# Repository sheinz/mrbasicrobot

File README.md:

mrbasicrobot
============

A robot based on Dagu Mr Basic platform.

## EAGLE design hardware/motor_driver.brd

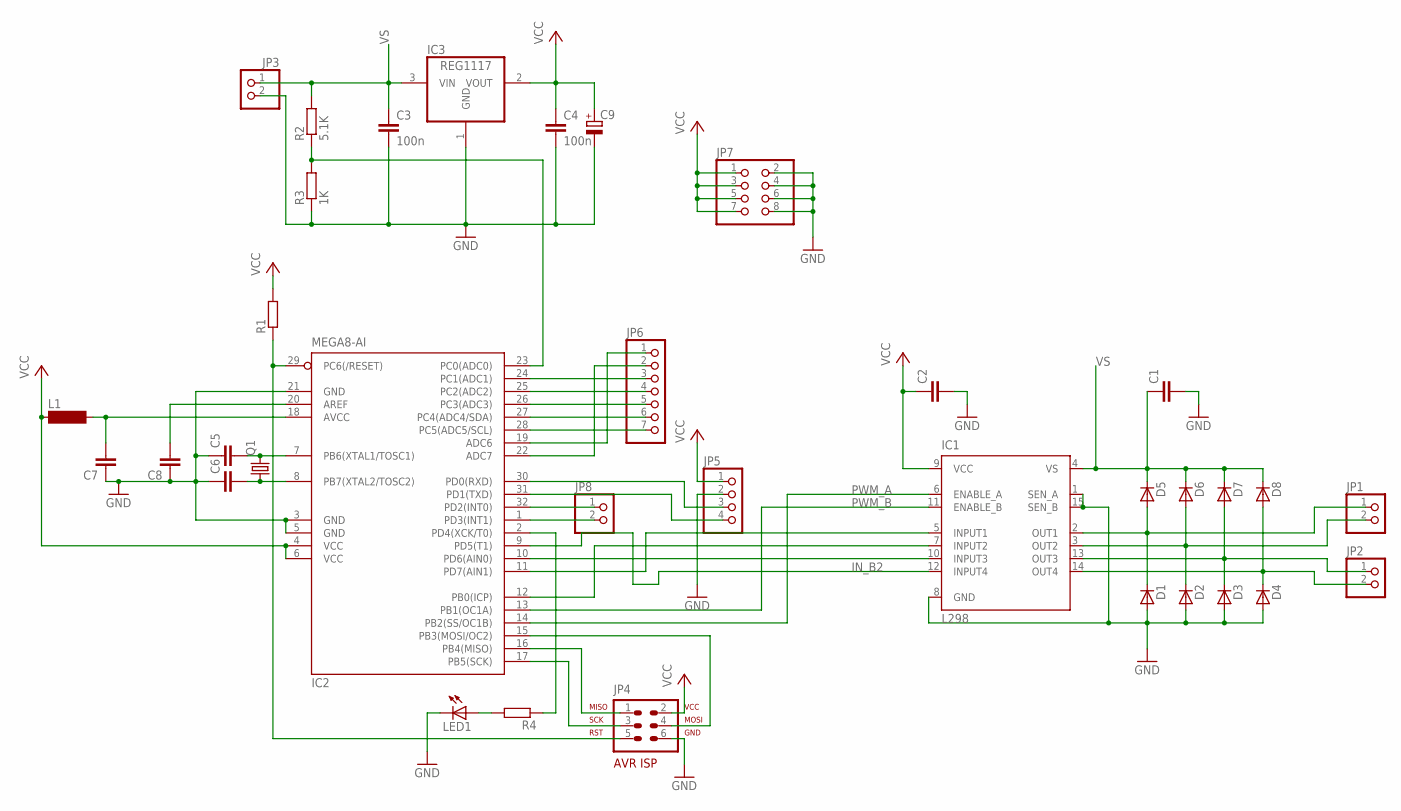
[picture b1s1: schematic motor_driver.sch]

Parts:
C1, C2, C5, C6, C7, C8: C-EUC0805; C0805
C3, C4: 100n; C0805
C9: CPOL-EUE2,5-6E; E2,5-6E
D1, D2, D3, D4, D5, D6, D7, D8: BYS10; SOD106A
IC1: L298; MULTIWATT-15
IC2: MEGA8-AI; TQFP32-08
IC3: REG1117; SOT223
JP1, JP2, JP3, JP8: PINHD-1X2; 1X02
JP4: AVR-ISP-6VERT; AVR-ISP-6
JP5: PINHD-1X4; 1X04
JP6: PINHD-1X7; 1X07
JP7: PINHD-2X4; 2X04
L1: SM-1206
LED1: LED3MM
Q1: CRYSTALHC49S; HC49/S
R1, R4: R-EU_M0805; M0805
R2: 5.1K; M0805
R3: 1K; M0805

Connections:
GND: C1.2, C2.2, C3.2, C4.2, C5.1, C6.1, C7.1, C8.1, C9.-, D1.A, D2.A, D3.A, D4.A, IC1.1 (SEN_A), IC1.8 (GND), IC1.15 (SEN_B), IC2.3 (GND), IC2.5 (GND), IC2.21 (GND), IC3.1 (GND), JP3.2, JP4.6, JP5.2, JP7.2, JP7.4, JP7.6, JP7.8, LED1.K (C), R3.1
IN_B2: IC1.12 (INPUT4), IC2.9 (PD5(T1))
unnamed: D1.K, D5.A, IC1.2 (OUT1), JP1.1
unnamed: D2.K, D6.A, IC1.3 (OUT2), JP1.2
unnamed: D3.K, D7.A, IC1.13 (OUT3), JP2.1
unnamed: D4.K, D8.A, IC1.14 (OUT4), JP2.2
unnamed: IC2.16 (PB4(MISO)), JP4.1
unnamed: IC2.17 (PB5(SCK)), JP4.3
unnamed: IC2.15 (PB3(MOSI/OC2)), JP4.4
unnamed: C5.2, IC2.7 (PB6(XTAL1/TOSC1)), Q1.2
unnamed: IC2.23 (PC0(ADC0)), R2.1, R3.2
unnamed: IC2.29 (PC6(/RESET)), JP4.5, R1.1
unnamed: C6.2, IC2.8 (PB7(XTAL2/TOSC2)), Q1.1
unnamed: IC2.30 (PD0(RXD)), JP5.3
unnamed: C7.2, IC2.18 (AVCC), L1.2
unnamed: C8.2, IC2.20 (AREF)
unnamed: IC2.31 (PD1(TXD)), JP5.4
unnamed: IC2.28 (PC5(ADC5/SCL)), JP6.7
unnamed: IC2.27 (PC4(ADC4/SDA)), JP6.6
unnamed: IC2.26 (PC3(ADC3)), JP6.5
unnamed: IC2.25 (PC2(ADC2)), JP6.4
unnamed: IC2.24 (PC1(ADC1)), JP6.3
unnamed: IC2.19 (ADC6), JP6.1
unnamed: IC2.22 (ADC7), JP6.2
unnamed: IC2.2 (PD4(XCK/T0)), R4.1
unnamed: IC1.7 (INPUT2), IC2.12 (PB0(ICP))
unnamed: IC1.5 (INPUT1), IC2.11 (PD7(AIN1))
unnamed: IC1.10 (INPUT3), IC2.10 (PD6(AIN0))
unnamed: LED1.A, R4.2
unnamed: IC2.32 (PD2(INT0)), JP8.1
unnamed: IC2.1 (PD3(INT1)), JP8.2
PWM_A: IC1.11 (ENABLE_B), IC2.13 (PB1(OC1A))
PWM_B: IC1.6 (ENABLE_A), IC2.14 (PB2(SS/OC1B))
VCC: C2.1, C4.1, C9.+, IC1.9 (VCC), IC2.4 (VCC), IC2.6 (VCC), IC3.2 (VOUT), JP4.2, JP5.1, JP7.1, JP7.3, JP7.5, JP7.7, L1.1, R1.2
VS: C1.1, C3.1, D5.K, D6.K, D7.K, D8.K, IC1.4 (VS), IC3.3 (VIN), JP3.1, R2.2

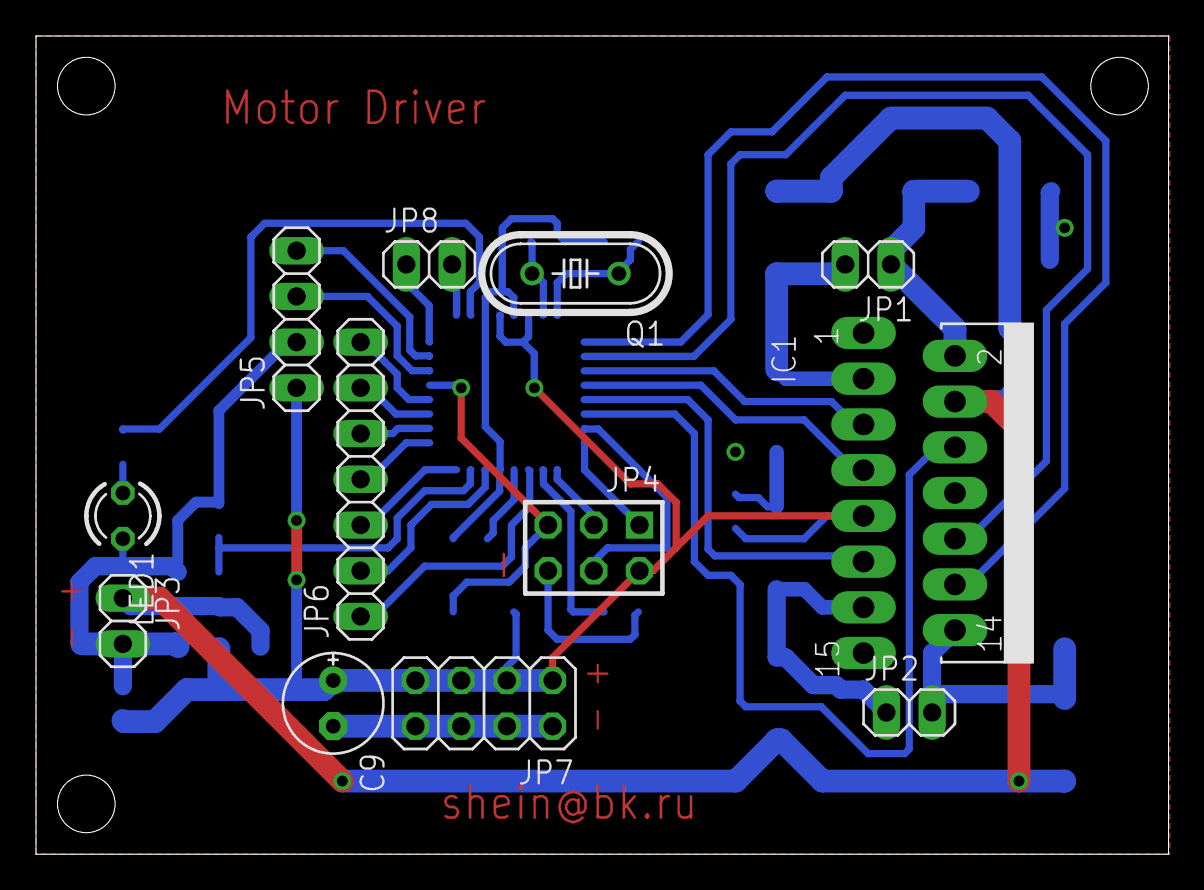
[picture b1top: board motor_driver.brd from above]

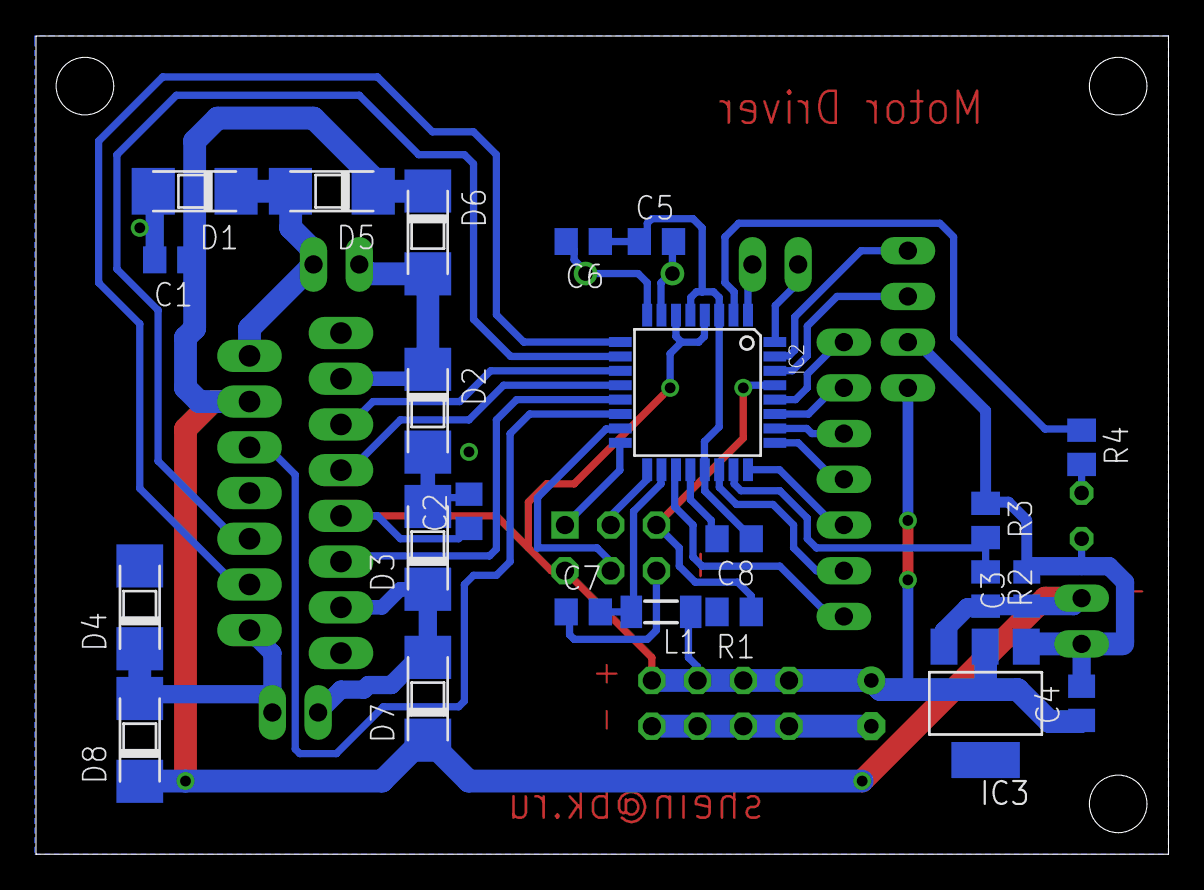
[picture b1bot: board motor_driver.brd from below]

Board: 2 copper layers, 62.9 x 45.5 mm, 35 parts (23 on the bottom side), 35 nets.

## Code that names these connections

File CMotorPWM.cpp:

/*
   The class uses Timer/Counter1 to orginise 2 channel PWM in order to control 2 motors

*/


#include "CMotorPWM.h"
#include <avr/io.h>
#include <avr/interrupt.h>


// hardware configuration
#define OUT_1_DDR      DDRD
#define OUT_1_PORT     PORTD
#define OUT_1_PIN      _BV(PD7)

#define OUT_2_DDR      DDRB
#define OUT_2_PORT     PORTB
#define OUT_2_PIN      _BV(PB0)

#define OUT_3_DDR      DDRD
#define OUT_3_PORT     PORTD
#define OUT_3_PIN      _BV(PD6)

#define OUT_4_DDR      DDRD
#define OUT_4_PORT     PORTD
#define OUT_4_PIN      _BV(PD5)

#define PWM_DDR        DDRB
#define PWM_PORT       PORTB
#define PWM_A_PIN      _BV(PB1)
#define PWM_B_PIN      _BV(PB2)

//    Motor PWM configuration
//    Motor A  - PB1
//    Motor B  - PB2


#define START_TIMER()      TCCR2 |= _BV(CS21) | _BV(CS22)   // Normal mode, prescaler F_CPU/8
#define STOP_TIMER()       TCCR2 = 0            // Stop timer

// clear the interrupt flag in case the interrupt has already occurred
#define ENABLE_OVERFLOW_INT()      TIFR |= _BV(TOV2); TIMSK |= _BV(TOIE2); TIMSK &= ~_BV(OCIE2)        // enable overflow
#define ENABLE_COMPARE_INT()       TIFR |= _BV(OCF2); TIMSK |= _BV(OCIE2); TIMSK &= ~_BV(TOIE2)    

CMotorPWM::eMotorMode CMotorPWM::mMotorMode[CMotorPWM::MOTOR_COUNT];
uint8_t CMotorPWM::mMotorSpeed[CMotorPWM::MOTOR_COUNT];
CMotorPWM::PwmChannel CMotorPWM::mPwm[CMotorPWM::MOTOR_COUNT];
int8_t CMotorPWM::mCurrentPwm;
CMotorPWM::PwmChannel CMotorPWM::mPwmUpd[CMotorPWM::MOTOR_COUNT];
volatile bool CMotorPWM::mUpdate;


// ----------------------------------------------------------------------------

ISR(TIMER2_COMP_vect)
{
   STOP_TIMER();
   TCNT2 = OCR2;     // reset the interrupt overhead

   PWM_PORT &= ~(CMotorPWM::mPwm[CMotorPWM::mCurrentPwm].mask);
  
   CMotorPWM::mCurrentPwm++;

   if (  (CMotorPWM::mCurrentPwm < CMotorPWM::MOTOR_COUNT) && 
         (CMotorPWM::mPwm[CMotorPWM::mCurrentPwm].mask != 0)   )
   {
      OCR2 = CMotorPWM::mPwm[CMotorPWM::mCurrentPwm].value;
   }
   else
   {
      //if (OCR2 == 0xFF) TCNT2 = 0xFF;     // so the next interrupt will be immediately 

      CMotorPWM::mCurrentPwm = 0;
      ENABLE_OVERFLOW_INT();
   }  


   START_TIMER();
}

// ----------------------------------------------------------------------------

ISR(TIMER2_OVF_vect)
{   
   uint8_t mask = 0;
   STOP_TIMER();
   TCNT2 = 0;        // reset interrupt overhead

   // update 
   if (CMotorPWM::mUpdate)
   {
      PORTC |= _BV(PC3);

      for (uint8_t i = 0; i < CMotorPWM::MOTOR_COUNT; i++)
      {
         CMotorPWM::mPwm[i].mask = CMotorPWM::mPwmUpd[i].mask;
         CMotorPWM::mPwm[i].value = CMotorPWM::mPwmUpd[i].value;
      }
      CMotorPWM::mUpdate = false;
   }
   
   if (CMotorPWM::mPwm[0].value == 0)
   {
      mask = CMotorPWM::mPwm[0].mask;
      CMotorPWM::mCurrentPwm = 1;   
   }
   
   OCR2 = CMotorPWM::mPwm[CMotorPWM::mCurrentPwm].value;    // it can be 0xFF

   PWM_PORT |= (PWM_A_PIN | PWM_B_PIN) & (~mask);  // set all pins except for the value=0
   
   ENABLE_COMPARE_INT();
   START_TIMER();
}

// ----------------------------------------------------------------------------

void CMotorPWM::init(void)
{
   // Set all control port to output
   OUT_1_DDR |= OUT_1_PIN;
   OUT_2_DDR |= OUT_2_PIN;
   OUT_3_DDR |= OUT_3_PIN;
   OUT_4_DDR |= OUT_4_PIN;

   PWM_DDR |= PWM_A_PIN | PWM_B_PIN; // the PWM pins must be set as output


   for (uint8_t i = 0; i < MOTOR_COUNT; i++)
   {
      mMotorSpeed[i] = 127;
      mMotorMode[i] = IDLE; 
   }
   
   mPwm[0].mask = PWM_A_PIN | PWM_B_PIN;
   mPwm[0].value = 127;
   mPwm[1].mask = 0;    // 0 means this is the terminal element
   mPwm[1].value = 0xFF;
   mPwmUpd[0] = mPwm[0];
   mPwmUpd[1] = mPwm[1];
   mUpdate = false;

   CMotorPWM::mCurrentPwm = 0;

   TCNT2 = 250;         // next interrupt will be the overflow
   OCR2 = 127;          // somewhere in the middle
   ENABLE_OVERFLOW_INT();
   START_TIMER();
}

// ----------------------------------------------------------------------------

void CMotorPWM::setMotor(const CMotorPWM::eMotor motor, const CMotorPWM::eMotorMode mode)
{
   if (motor < MOTOR_COUNT)
   {
      mMotorMode[motor] = mode;

      if (mode == IDLE)
      {
         mMotorSpeed[motor] = 0;
         updateMotorsSpeed();
      }
      else if (mode == FORWARD)
      {
         setDirection(motor, true, false);
         updateMotorsSpeed();
      }
      else if (mode == BACKWARD)
      {
         setDirection(motor, false, true);
         updateMotorsSpeed();
      }
      else if (mode == BRAKE)
      {
         setDirection(motor, false, false);
         mMotorSpeed[motor] = 0xFF;
         updateMotorsSpeed();
      }
   }   
}

// ----------------------------------------------------------------------------

void CMotorPWM::setMotor(const CMotorPWM::eMotor motor, const CMotorPWM::eMotorMode mode, const uint8_t speed)
{
   if (motor < MOTOR_COUNT)
   {
      mMotorSpeed[motor] = speed;
      setMotor(motor, mode);
   }
}

// ----------------------------------------------------------------------------

void CMotorPWM::updateMotorsSpeed(void)
{
   while (mUpdate);     // wait untel the previous update cycle ends

   if (mMotorSpeed[0] < mMotorSpeed[1])
   {
      mPwmUpd[0].value = mMotorSpeed[0];
      mPwmUpd[0].mask = PWM_A_PIN;
      mPwmUpd[1].value = mMotorSpeed[1];
      mPwmUpd[1].mask = PWM_B_PIN;
   }
   else if (mMotorSpeed[0] > mMotorSpeed[1])
   {
      mPwmUpd[0].value = mMotorSpeed[1];
      mPwmUpd[0].mask = PWM_B_PIN;
      mPwmUpd[1].value = mMotorSpeed[0];
      mPwmUpd[1].mask = PWM_A_PIN;
   }
   else     // equal
   {
      mPwmUpd[0].value = mMotorSpeed[0];
      mPwmUpd[0].mask = PWM_B_PIN | PWM_A_PIN;
      mPwmUpd[1].value = 0xFF;
      mPwmUpd[1].mask = 0;
   }

   uint8_t sreg = SREG;
   cli();
   mUpdate = true;      // safe set the flag
   SREG = sreg;
}
// ----------------------------------------------------------------------------
void CMotorPWM::setDirection(const eMotor motor, const bool out1, const bool out2)
{
   if (motor == MOTOR_A)
   {
      if (out1 == true)
      {
         OUT_1_PORT |= OUT_1_PIN;      // set pin
      }
      else
      {
         OUT_1_PORT &= ~OUT_1_PIN;     // clear pin
      }

      if (out2 == true)
      {
         OUT_2_PORT |= OUT_2_PIN;      // set pin
      }
      else
      {
         OUT_2_PORT &= ~OUT_2_PIN;     // clear pin
      }
   }
   else if (motor == MOTOR_B)
   {
      if (out1 == true)
      {
         OUT_3_PORT |= OUT_3_PIN;      // set pin
      }
      else
      {
         OUT_3_PORT &= ~OUT_3_PIN;     // clear pin
      }

      if (out2 == true)
      {
         OUT_4_PORT |= OUT_4_PIN;      // set pin
      }
      else
      {
         OUT_4_PORT &= ~OUT_4_PIN;     // clear pin
      }
   }
}

// ----------------------------------------------------------------------------

uint8_t CMotorPWM::getMotorSpeed(const eMotor motor)
{
   if (motor < MOTOR_COUNT)
   {
      return mMotorSpeed[motor];
   }
   else
   {
      return 0;
   }
}

// ----------------------------------------------------------------------------

uint8_t CMotorPWM::increaseMotorSpeed(const eMotor motor, uint8_t step)
{
   if (motor < MOTOR_COUNT)
   {
      if ( (0xFF - mMotorSpeed[motor]) > step )
      {
         mMotorSpeed[motor] = 0xFF;
      }
      else
      {
         mMotorSpeed[motor] += step;
      }

      updateMotorsSpeed();

      return mMotorSpeed[motor];
   }
   else
   {
      return 0;
   }
}

// ----------------------------------------------------------------------------

uint8_t CMotorPWM::decreaseMotorSpeed(const eMotor motor, uint8_t step)
{
   if (motor < MOTOR_COUNT)
   {
      if (mMotorSpeed[motor] < step)
      {
         mMotorSpeed[motor] = 0;
      }
      else
      {
         mMotorSpeed[motor] -= step;
      }

      updateMotorsSpeed();

      return mMotorSpeed[motor];
   }
   else
   {
      return 0;
   }
}

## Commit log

2013-10-05 Source files move into src directory
2013-10-05 Moved obj files into obj directory
2013-10-05 Added schematic and board
2013-10-06 Changed Motor PWM implementation. Using hardware PWM.
2013-10-06 Added eclipse project files
2013-10-06 Added servo support. Lightweigh servo controller. Controlls only one servo
